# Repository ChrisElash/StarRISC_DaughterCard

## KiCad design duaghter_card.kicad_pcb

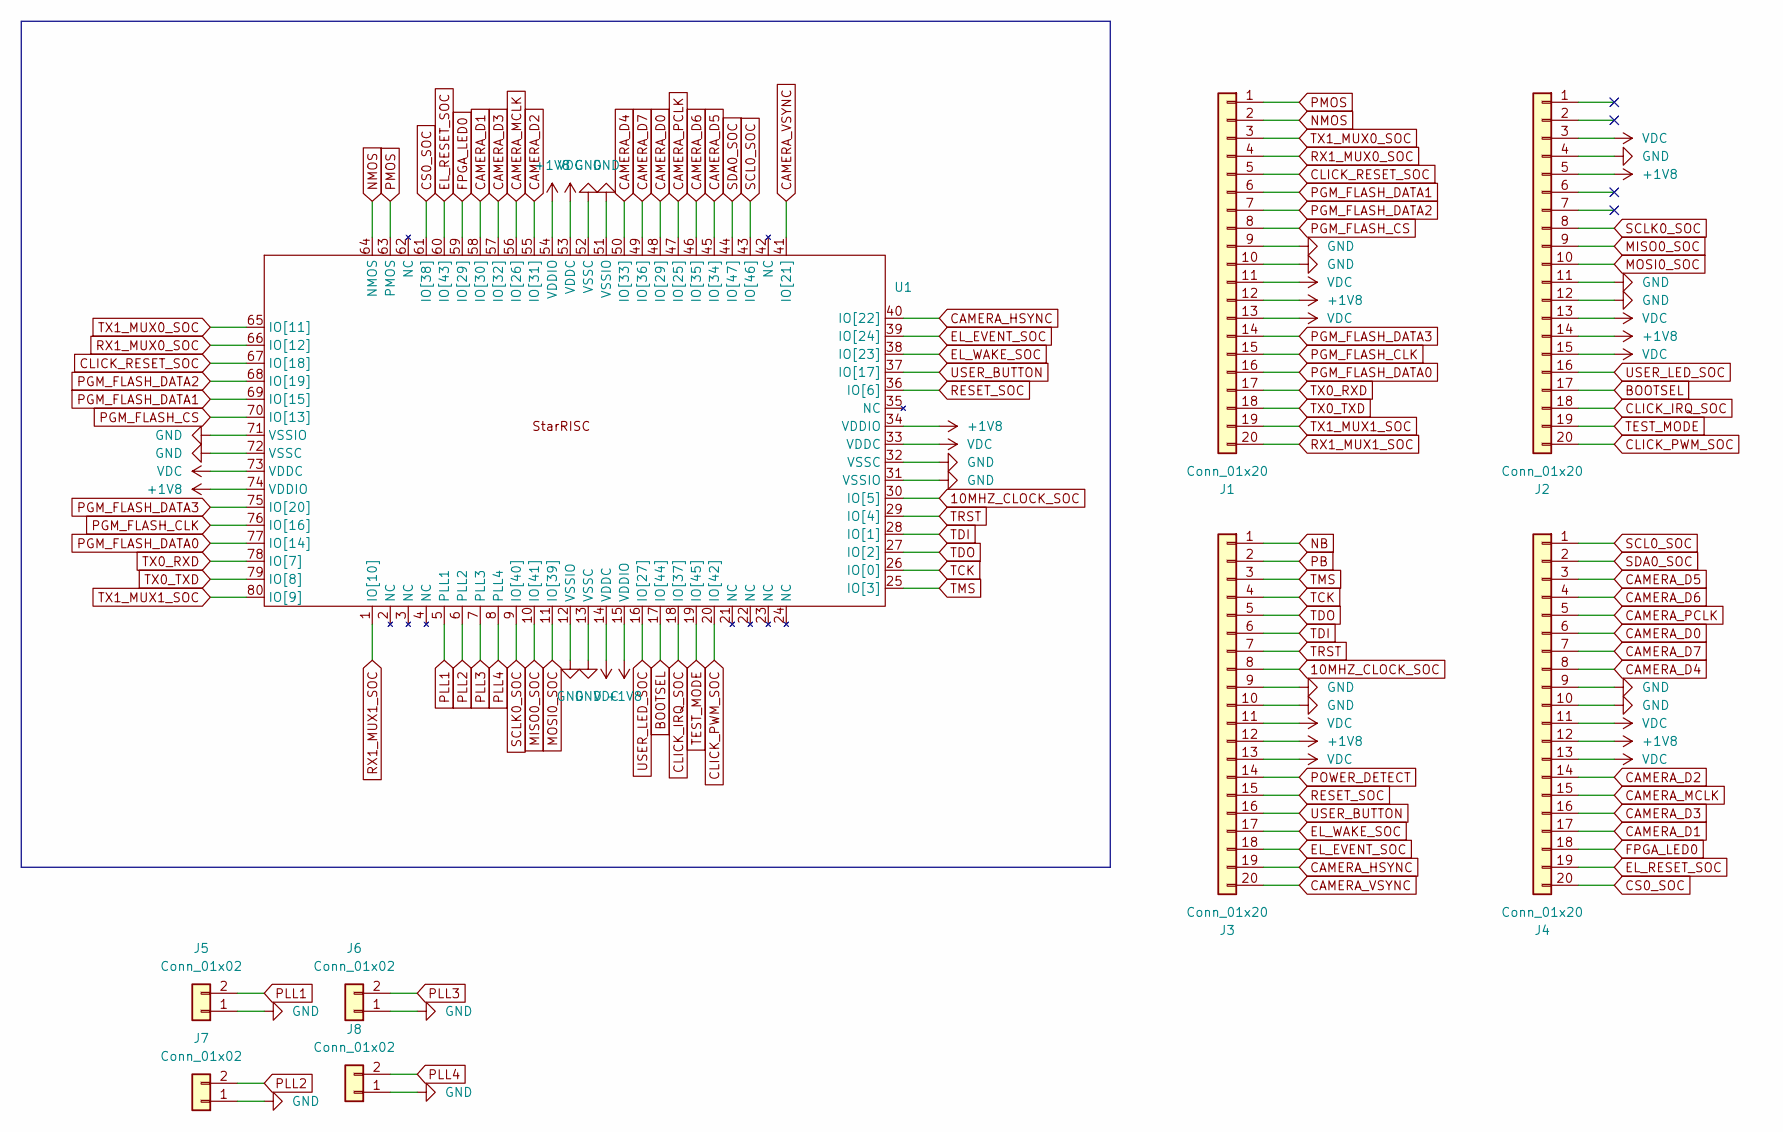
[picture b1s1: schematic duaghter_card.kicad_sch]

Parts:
J1, J2, J3, J4: Conn_01x20; PinSocket_1x20_P1.00mm_Vertical
J5, J6, J7, J8: Conn_01x02; PinHeader_1x02_P2.54mm_Vertical
U1: 80CQFP

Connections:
10MHZ_CLOCK_SOC: J3.8, U1.30 (IO[5])
+1V8: J1.12, J2.5, J2.14, J3.12, J4.12, U1.15 (VDDIO), U1.34 (VDDIO), U1.54 (VDDIO), U1.74 (VDDIO)
BOOTSEL: J2.17, U1.17 (IO[44])
CAMERA_D0: J4.6, U1.48 (IO[29])
CAMERA_D1: J4.17, U1.58 (IO[30])
CAMERA_D2: J4.14, U1.55 (IO[31])
CAMERA_D3: J4.16, U1.57 (IO[32])
CAMERA_D4: J4.8, U1.50 (IO[33])
CAMERA_D5: J4.3, U1.45 (IO[34])
CAMERA_D6: J4.4, U1.46 (IO[35])
CAMERA_D7: J4.7, U1.49 (IO[36])
CAMERA_HSYNC: J3.19, U1.40 (IO[22])
CAMERA_MCLK: J4.15, U1.56 (IO[26])
CAMERA_PCLK: J4.5, U1.47 (IO[25])
CAMERA_VSYNC: J3.20, U1.41 (IO[21])
CLICK_IRQ_SOC: J2.18, U1.18 (IO[37])
CLICK_PWM_SOC: J2.20, U1.20 (IO[42])
CLICK_RESET_SOC: J1.5, U1.67 (IO[18])
CS0_SOC: J4.20, U1.61 (IO[38])
EL_EVENT_SOC: J3.18, U1.39 (IO[24])
EL_RESET_SOC: J4.19, U1.60 (IO[43])
EL_WAKE_SOC: J3.17, U1.38 (IO[23])
FPGA_LED0: J4.18, U1.59 (IO[29])
GND: J1.9, J1.10, J2.4, J2.11, J2.12, J3.9, J3.10, J4.9, J4.10, J5.1, J6.1, J7.1, J8.1, U1.12 (VSSIO), U1.13 (VSSC), U1.31 (VSSIO), U1.32 (VSSC), U1.51 (VSSIO), U1.52 (VSSC), U1.71 (VSSIO), U1.72 (VSSC)
MISO0_SOC: J2.9, U1.10 (IO[41])
MOSI0_SOC: J2.10, U1.11 (IO[39])
NB: J3.1
NMOS: J1.2, U1.64 (NMOS)
PB: J3.2
PGM_FLASH_CLK: J1.15, U1.76 (IO[16])
PGM_FLASH_CS: J1.8, U1.70 (IO[13])
PGM_FLASH_DATA0: J1.16, U1.77 (IO[14])
PGM_FLASH_DATA1: J1.6, U1.69 (IO[15])
PGM_FLASH_DATA2: J1.7, U1.68 (IO[19])
PGM_FLASH_DATA3: J1.14, U1.75 (IO[20])
PLL1: J5.2, U1.5 (PLL1)
PLL2: J7.2, U1.6 (PLL2)
PLL3: J6.2, U1.7 (PLL3)
PLL4: J8.2, U1.8 (PLL4)
PMOS: J1.1, U1.63 (PMOS)
POWER_DETECT: J3.14
RESET_SOC: J3.15, U1.36 (IO[6])
RX1_MUX0_SOC: J1.4, U1.66 (IO[12])
RX1_MUX1_SOC: J1.20, U1.1 (IO[10])
SCL0_SOC: J4.1, U1.43 (IO[46])
SCLK0_SOC: J2.8, U1.9 (IO[40])
SDA0_SOC: J4.2, U1.44 (IO[47])
TCK: J3.4, U1.26 (IO[0])
TDI: J3.6, U1.28 (IO[1])
TDO: J3.5, U1.27 (IO[2])
TEST_MODE: J2.19, U1.19 (IO[45])
TMS: J3.3, U1.25 (IO[3])
TRST: J3.7, U1.29 (IO[4])
TX0_RXD: J1.17, U1.78 (IO[7])
TX0_TXD: J1.18, U1.79 (IO[8])
TX1_MUX0_SOC: J1.3, U1.65 (IO[11])
TX1_MUX1_SOC: J1.19, U1.80 (IO[9])
USER_BUTTON: J3.16, U1.37 (IO[17])
USER_LED_SOC: J2.16, U1.16 (IO[27])
VDC: J1.11, J1.13, J2.3, J2.13, J2.15, J3.11, J3.13, J4.11, J4.13, U1.14 (VDDC), U1.33 (VDDC), U1.53 (VDDC), U1.73 (VDDC)

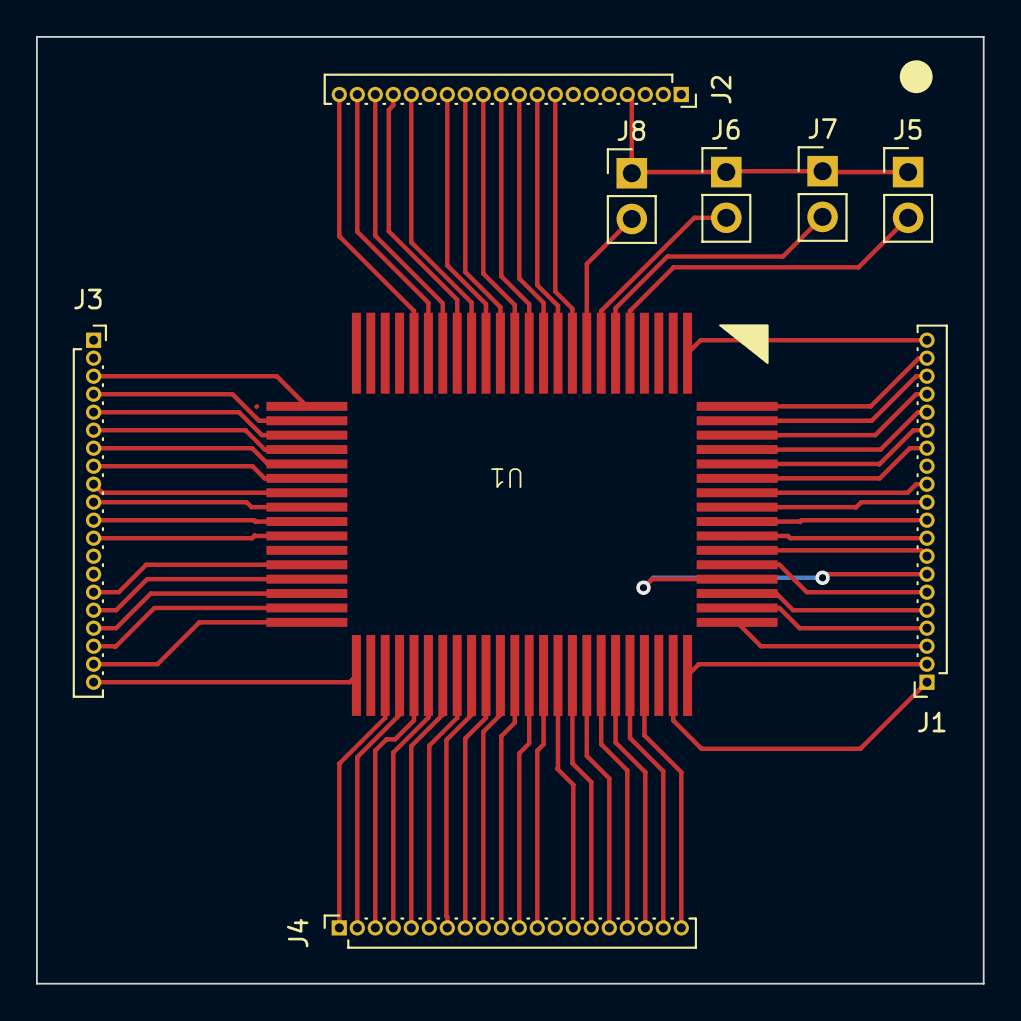
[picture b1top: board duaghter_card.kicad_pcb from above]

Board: 2 copper layers, 52.6 x 52.6 mm, 9 parts (0 on the bottom side), 57 nets.
